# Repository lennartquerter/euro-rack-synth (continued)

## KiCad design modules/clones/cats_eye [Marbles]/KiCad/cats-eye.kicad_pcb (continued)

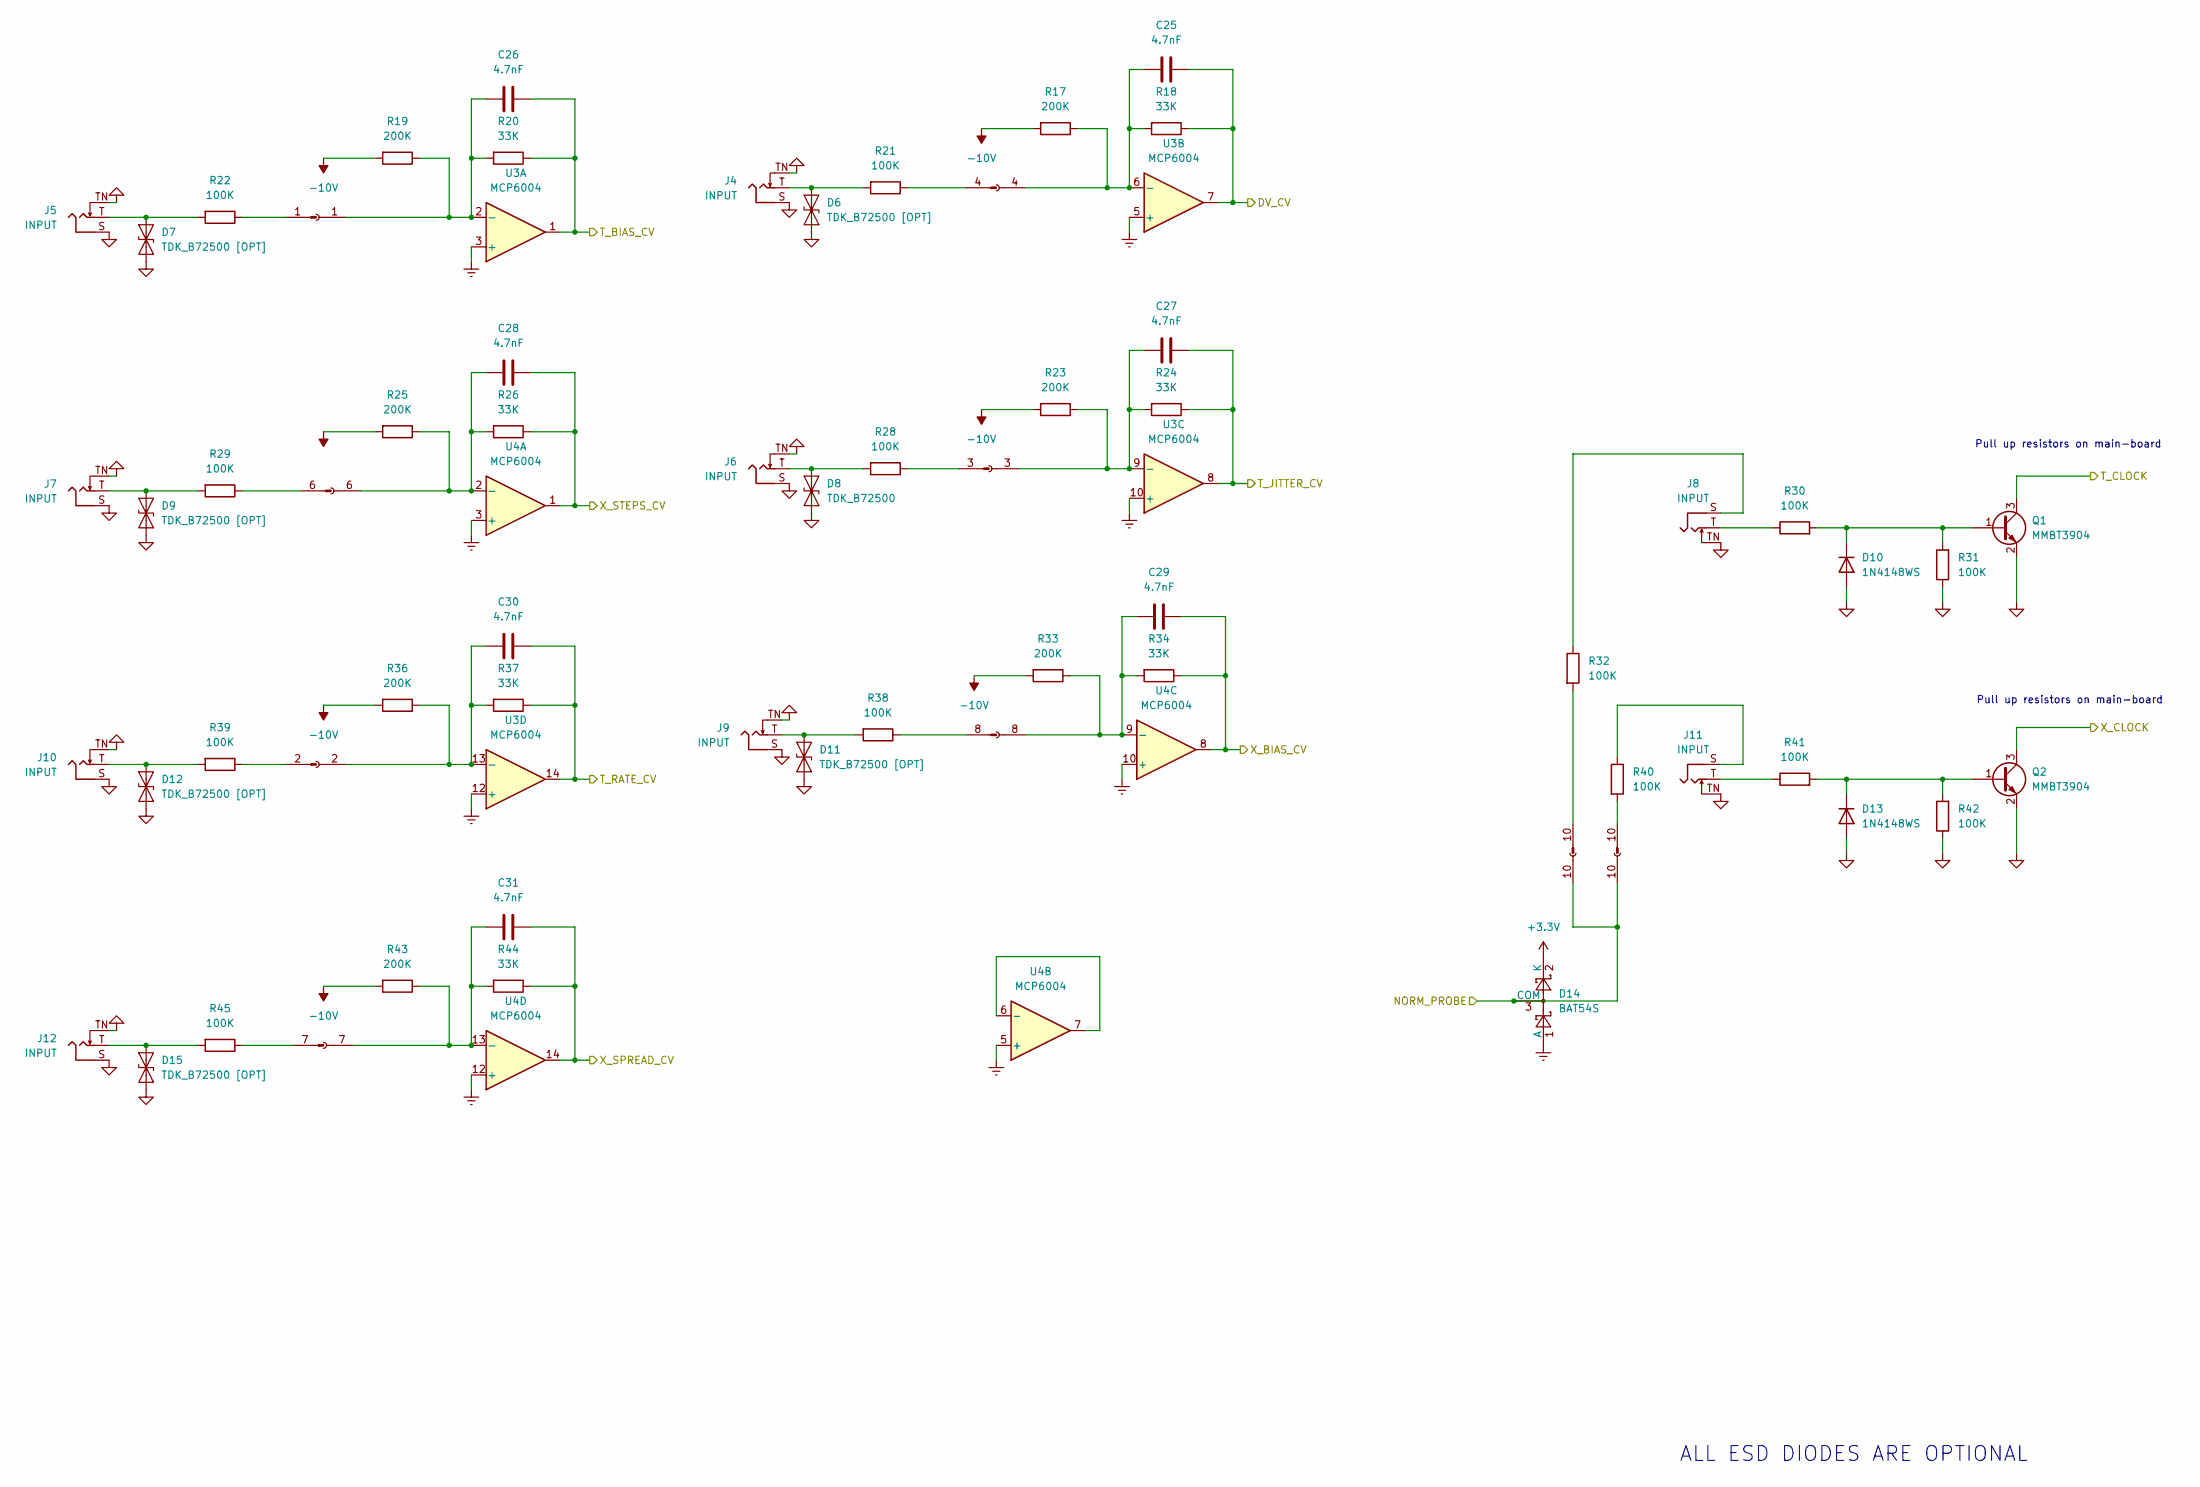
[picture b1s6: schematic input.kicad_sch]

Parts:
C25, C26, C27, C28, C29, C30, C31: 4.7nF; C_0805_2012Metric_Pad1.18x1.45mm_HandSolder
D6, D7, D9, D11, D12, D15: TDK_B72500 [OPT]; D_0603_1608Metric_Pad1.05x0.95mm_HandSolder
D8: TDK_B72500; D_0603_1608Metric_Pad1.05x0.95mm_HandSolder
D10, D13: 1N4148WS; D_SOD-323_HandSoldering
D14: BAT54S; SOT-23_Handsoldering
J4, J5, J6, J7, J8, J9, J10, J11, J12: INPUT; Jack_3.5mm_QingPu_WQP-PJ398SM_Vertical_CircularHoles
Q1, Q2: MMBT3904; SOT-23_Handsoldering
R17, R19, R23, R25, R33, R36, R43: 200K; R_0805_2012Metric_Pad1.20x1.40mm_HandSolder
R18, R20, R24, R26, R34, R37, R44: 33K; R_0805_2012Metric_Pad1.20x1.40mm_HandSolder
R21, R22, R28, R29, R30, R31, R32, R38, R39, R40, R41, R42, R45: 100K; R_0805_2012Metric_Pad1.20x1.40mm_HandSolder
U3, U4: MCP6004; SOIC-14
XP1, XP3: Conn_01x16_Socket; PinSocket_1x16_P2.54mm_Vertical
XP2, XP4: Conn_01x16_Pin; PinHeader_1x16_P2.54mm_Vertical
XP5: Conn_01x08_Socket; PinSocket_1x08_P2.54mm_Vertical
XP6: Conn_01x08_Pin; PinHeader_1x08_P2.54mm_Vertical

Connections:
+3.3V: D14.2 (K); also elsewhere on the board
-10V: R17.2, R19.2, R23.2, R25.2, R33.2, R36.2, R43.2; also elsewhere on the board
/input/DV_CV: C25.1, R18.1, U3.7; also elsewhere on the board
/input/NORM_PROBE: D14.3 (COM), XP1.10, XP3.10; also elsewhere on the board
/input/T_BIAS_CV: C26.1, R20.1, U3.1; also elsewhere on the board
/input/T_CLOCK: Q1.3 (C); also elsewhere on the board
/input/T_JITTER_CV: C27.1, R24.1, U3.8; also elsewhere on the board
/input/T_RATE_CV: C30.1, R37.1, U3.14; also elsewhere on the board
/input/X_BIAS_CV: C29.1, R34.1, U4.8; also elsewhere on the board
/input/X_CLOCK: Q2.3 (C); also elsewhere on the board
/input/X_SPREAD_CV: C31.1, R44.1, U4.14; also elsewhere on the board
/input/X_STEPS_CV: C28.1, R26.1, U4.1; also elsewhere on the board
GND: D6.2 (A2), D7.2 (A2), D8.2 (A2), D9.2 (A2), D10.2 (A), D11.2 (A2), D12.2 (A2), D13.2 (A), D15.2 (A2), J4.S, J4.TN, J5.S, J5.TN, J6.S, J6.TN, J7.S, J7.TN, J8.TN, J9.S, J9.TN, J10.S, J10.TN, J11.TN, J12.S, J12.TN, Q1.2 (E), Q2.2 (E), R31.1, R42.1; also elsewhere on the board
GNDREF: D14.1 (A), U3.3 (+), U3.5 (+), U3.10 (+), U3.12 (+), U4.3 (+), U4.5 (+), U4.10 (+), U4.12 (+); also elsewhere on the board
unnamed: D6.1 (A1), J4.T, R21.2
unnamed: D7.1 (A1), J5.T, R22.2
unnamed: D8.1 (A1), J6.T, R28.2
unnamed: D9.1 (A1), J7.T, R29.2
unnamed: D10.1 (K), Q1.1 (B), R30.2, R31.2
unnamed: D11.1 (A1), J9.T, R38.2
unnamed: D12.1 (A1), J10.T, R39.2
unnamed: D13.1 (K), Q2.1 (B), R41.2, R42.2
unnamed: D15.1 (A1), J12.T, R45.2
unnamed: J8.S, R32.1
unnamed: J8.T, R30.1
unnamed: J11.S, R40.1
unnamed: J11.T, R41.1
unnamed: C26.2, R19.1, R20.2, U3.2 (-), XP5.1
unnamed: C25.2, R17.1, R18.2, U3.6 (-), XP5.4
unnamed: C27.2, R23.1, R24.2, U3.9 (-), XP5.3
unnamed: C30.2, R36.1, R37.2, U3.13 (-), XP5.2
unnamed: C28.2, R25.1, R26.2, U4.2 (-), XP5.6
unnamed: U4.6 (-), U4.7
unnamed: C29.2, R33.1, R34.2, U4.9 (-), XP5.8
unnamed: C31.2, R43.1, R44.2, U4.13 (-), XP5.7
unnamed: R32.2, XP2.10
unnamed: R40.2, XP4.10
unnamed: R22.1, XP6.1
unnamed: R39.1, XP6.2
unnamed: R28.1, XP6.3
unnamed: R21.1, XP6.4
unnamed: R29.1, XP6.6
unnamed: R45.1, XP6.7
unnamed: R38.1, XP6.8

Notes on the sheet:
ALL ESD DIODES ARE OPTIONAL
Pull up resistors on main-board

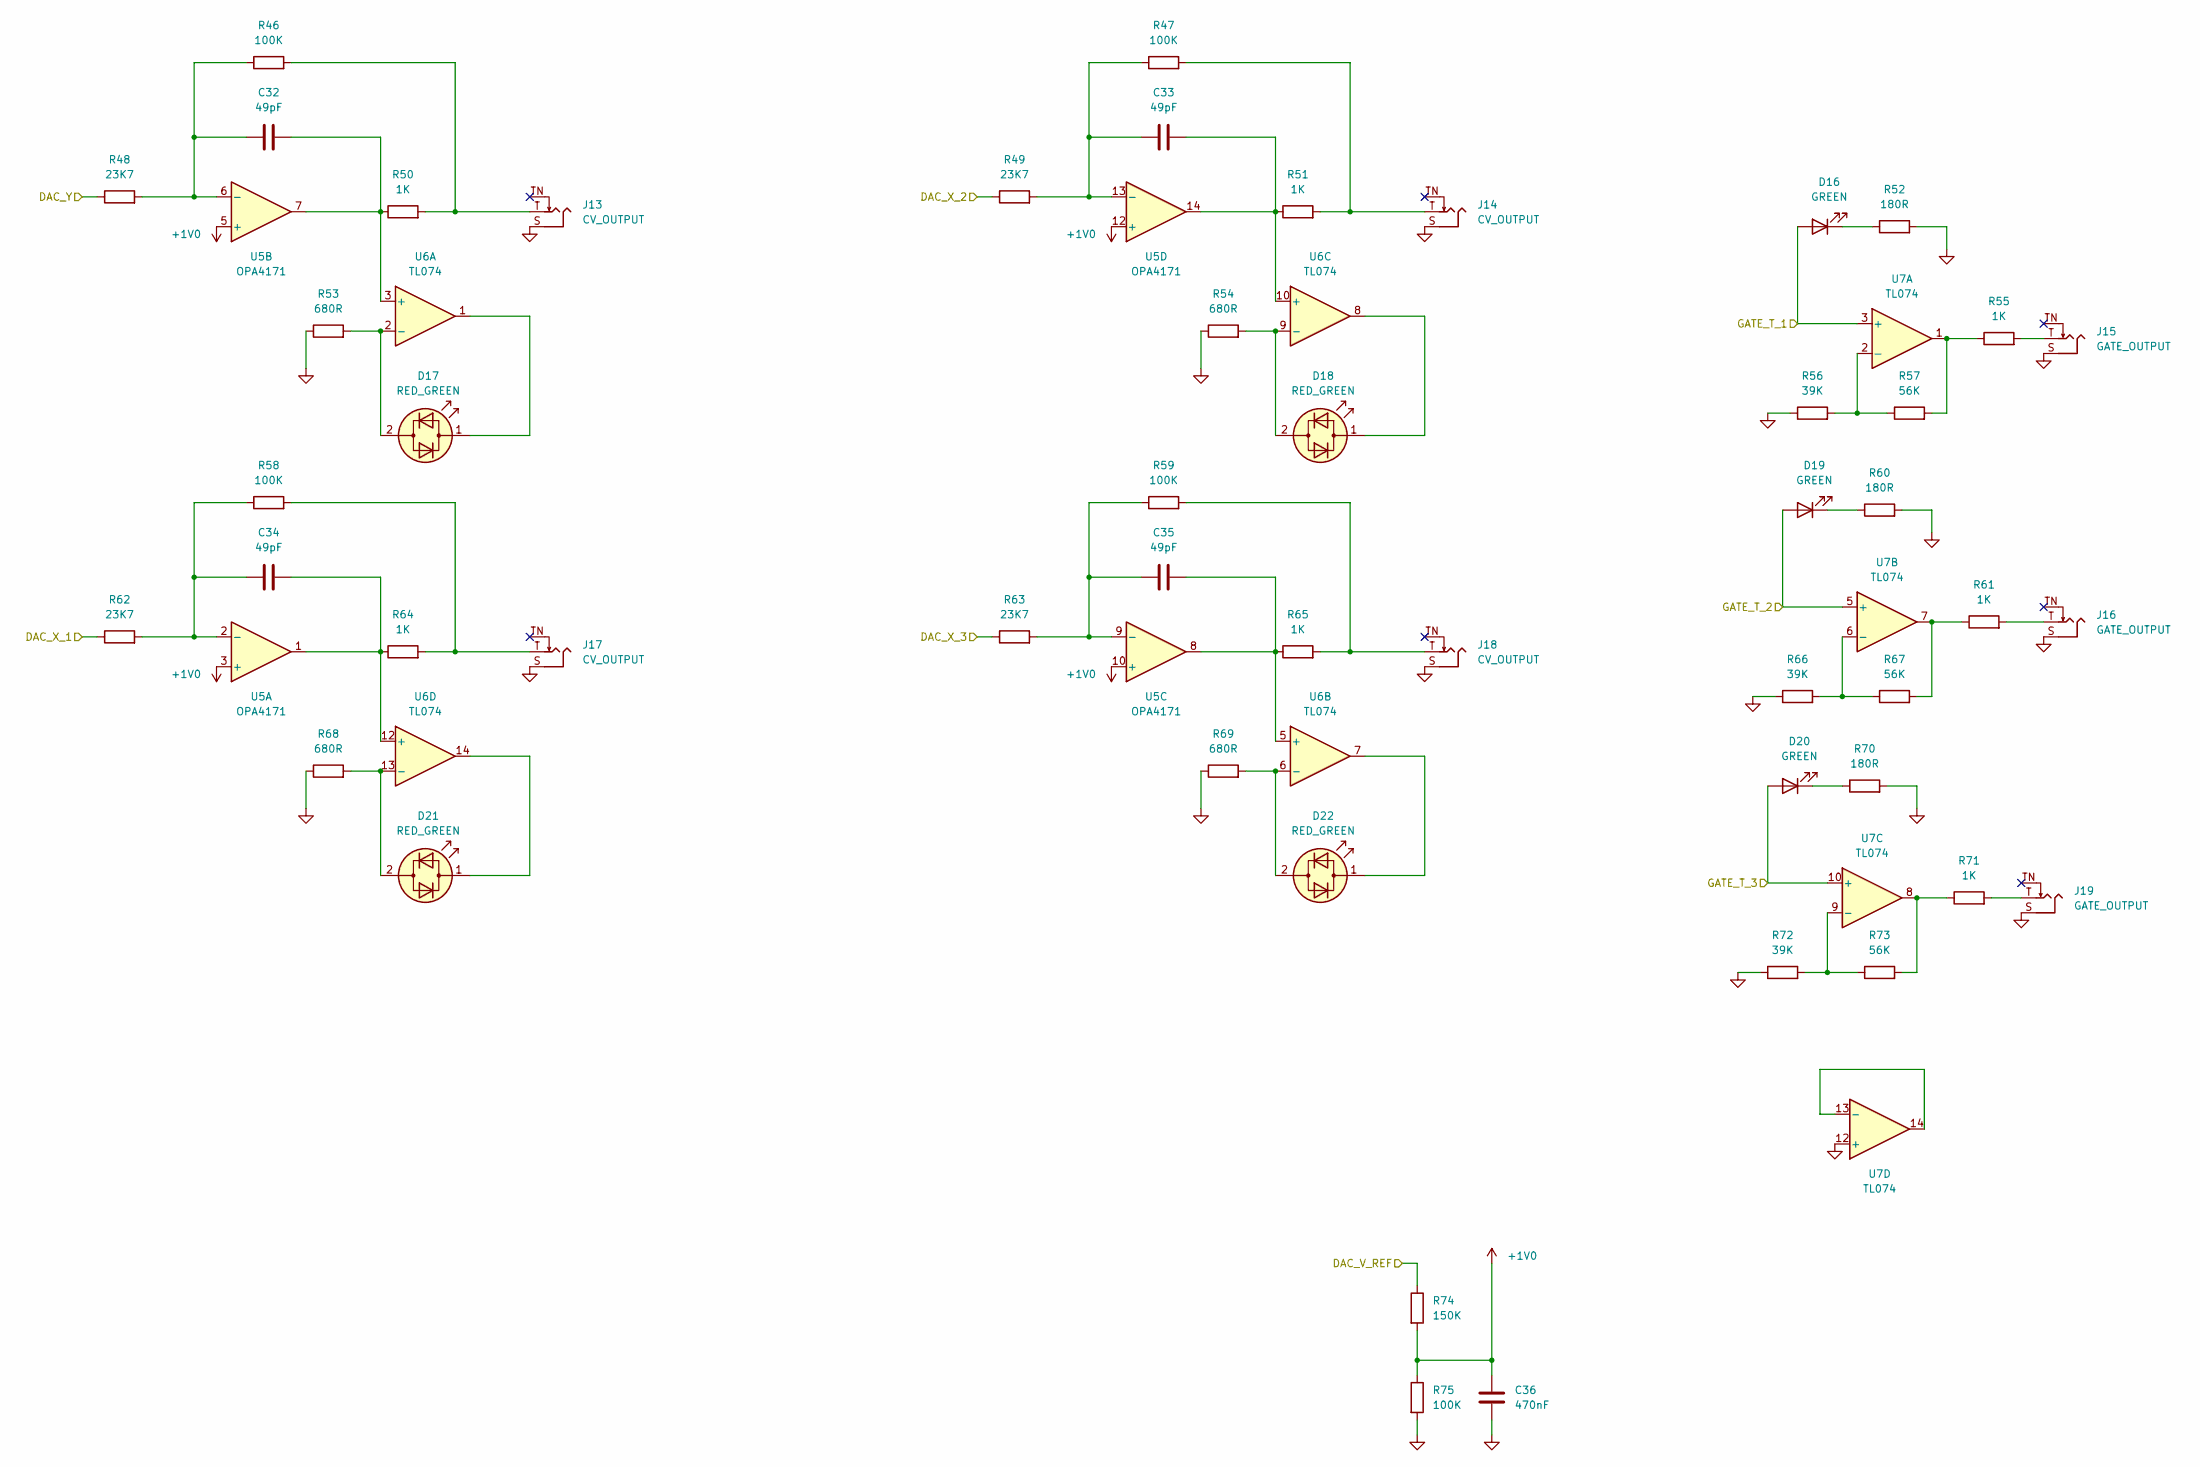
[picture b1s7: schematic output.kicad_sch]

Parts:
C32, C33, C34, C35: 49pF; C_0805_2012Metric_Pad1.18x1.45mm_HandSolder
C36: 470nF; C_0805_2012Metric_Pad1.18x1.45mm_HandSolder
D16, D19, D20: GREEN; LED_D3.0mm_SM
D17, D18, D21, D22: RED_GREEN; LED_D3.0mm_SM
J13, J14, J17, J18: CV_OUTPUT; Jack_3.5mm_QingPu_WQP-PJ398SM_SM
J15, J16, J19: GATE_OUTPUT; Jack_3.5mm_QingPu_WQP-PJ398SM_SM
R46, R47, R58, R59, R75: 100K; R_0805_2012Metric_Pad1.20x1.40mm_HandSolder
R48, R49, R62, R63: 23K7; R_0805_2012Metric_Pad1.20x1.40mm_HandSolder
R50, R51, R55, R61, R64, R65, R71: 1K; R_0805_2012Metric_Pad1.20x1.40mm_HandSolder
R52, R60, R70: 180R; R_0805_2012Metric_Pad1.20x1.40mm_HandSolder
R53, R54, R68, R69: 680R; R_0805_2012Metric_Pad1.20x1.40mm_HandSolder
R56, R66, R72: 39K; R_0805_2012Metric_Pad1.20x1.40mm_HandSolder
R57, R67, R73: 56K; R_0805_2012Metric_Pad1.20x1.40mm_HandSolder
R74: 150K; R_0805_2012Metric_Pad1.20x1.40mm_HandSolder
U5: OPA4171; SOIC-14
U6, U7: TL074; SOIC-14

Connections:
+1V0: C36.2, R74.2, R75.1, U5.3 (+), U5.5 (+), U5.10 (+), U5.12 (+)
/output/DAC_V_REF: R74.1; also elsewhere on the board
/output/DAC_X_1: R62.1; also elsewhere on the board
/output/DAC_X_2: R49.1; also elsewhere on the board
/output/DAC_X_3: R63.1; also elsewhere on the board
/output/DAC_Y: R48.1; also elsewhere on the board
/output/GATE_T_1: D16.2 (A), U7.3 (+); also elsewhere on the board
/output/GATE_T_2: D19.2 (A), U7.5 (+); also elsewhere on the board
/output/GATE_T_3: D20.2 (A), U7.10 (+); also elsewhere on the board
GND: C36.1, J13.S, J14.S, J15.S, J16.S, J17.S, J18.S, J19.S, R52.2, R53.1, R54.1, R56.1, R60.2, R66.1, R68.1, R69.1, R70.2, R72.1, R75.2, U7.12 (+); also elsewhere on the board
unnamed: D16.1 (K), R52.1
unnamed: D17.2 (AK), R53.2, U6.2 (-)
unnamed: D17.1 (KA), U6.1
unnamed: D18.2 (AK), R54.2, U6.9 (-)
unnamed: D18.1 (KA), U6.8
unnamed: D19.1 (K), R60.1
unnamed: D20.1 (K), R70.1
unnamed: D21.2 (AK), R68.2, U6.13 (-)
unnamed: D21.1 (KA), U6.14
unnamed: D22.2 (AK), R69.2, U6.6 (-)
unnamed: D22.1 (KA), U6.7
unnamed: J13.T, R46.2, R50.2
unnamed: J14.T, R47.2, R51.2
unnamed: J15.T, R55.2
unnamed: J16.T, R61.2
unnamed: J17.T, R58.2, R64.2
unnamed: J18.T, R59.2, R65.2
unnamed: J19.T, R71.2
unnamed: R55.1, R57.2, U7.1
unnamed: R61.1, R67.2, U7.7
unnamed: R71.1, R73.2, U7.8
unnamed: C34.2, R58.1, R62.2, U5.2 (-)
unnamed: C32.2, R46.1, R48.2, U5.6 (-)
unnamed: C35.2, R59.1, R63.2, U5.9 (-)
unnamed: C33.2, R47.1, R49.2, U5.13 (-)
unnamed: C32.1, R50.1, U5.7, U6.3 (+)
unnamed: C35.1, R65.1, U5.8, U6.5 (+)
unnamed: C33.1, R51.1, U5.14, U6.10 (+)
unnamed: C34.1, R64.1, U5.1, U6.12 (+)
unnamed: R56.2, R57.1, U7.2 (-)
unnamed: R66.2, R67.1, U7.6 (-)
unnamed: R72.2, R73.1, U7.9 (-)
unnamed: U7.13 (-), U7.14

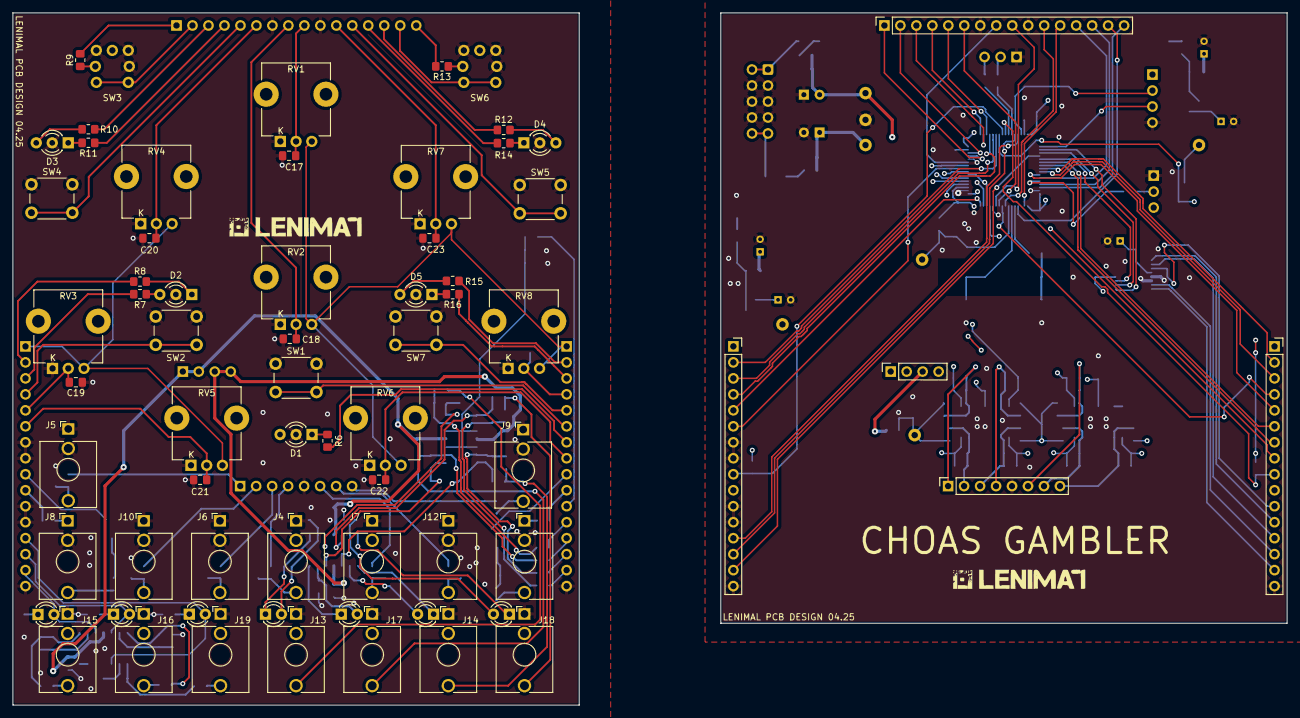
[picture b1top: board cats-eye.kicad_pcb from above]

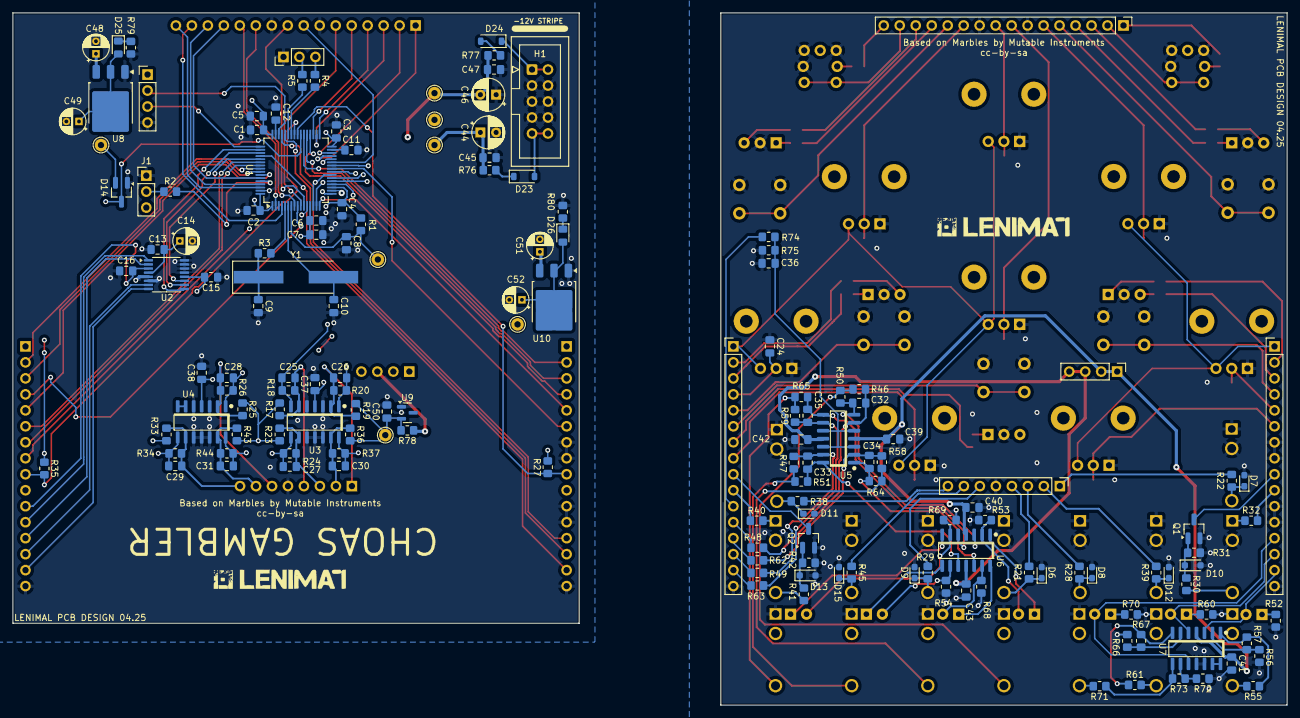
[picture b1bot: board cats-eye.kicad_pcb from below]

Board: 4 copper layers, 202.5 x 110.0 mm, 223 parts (157 on the bottom side), 188 nets.

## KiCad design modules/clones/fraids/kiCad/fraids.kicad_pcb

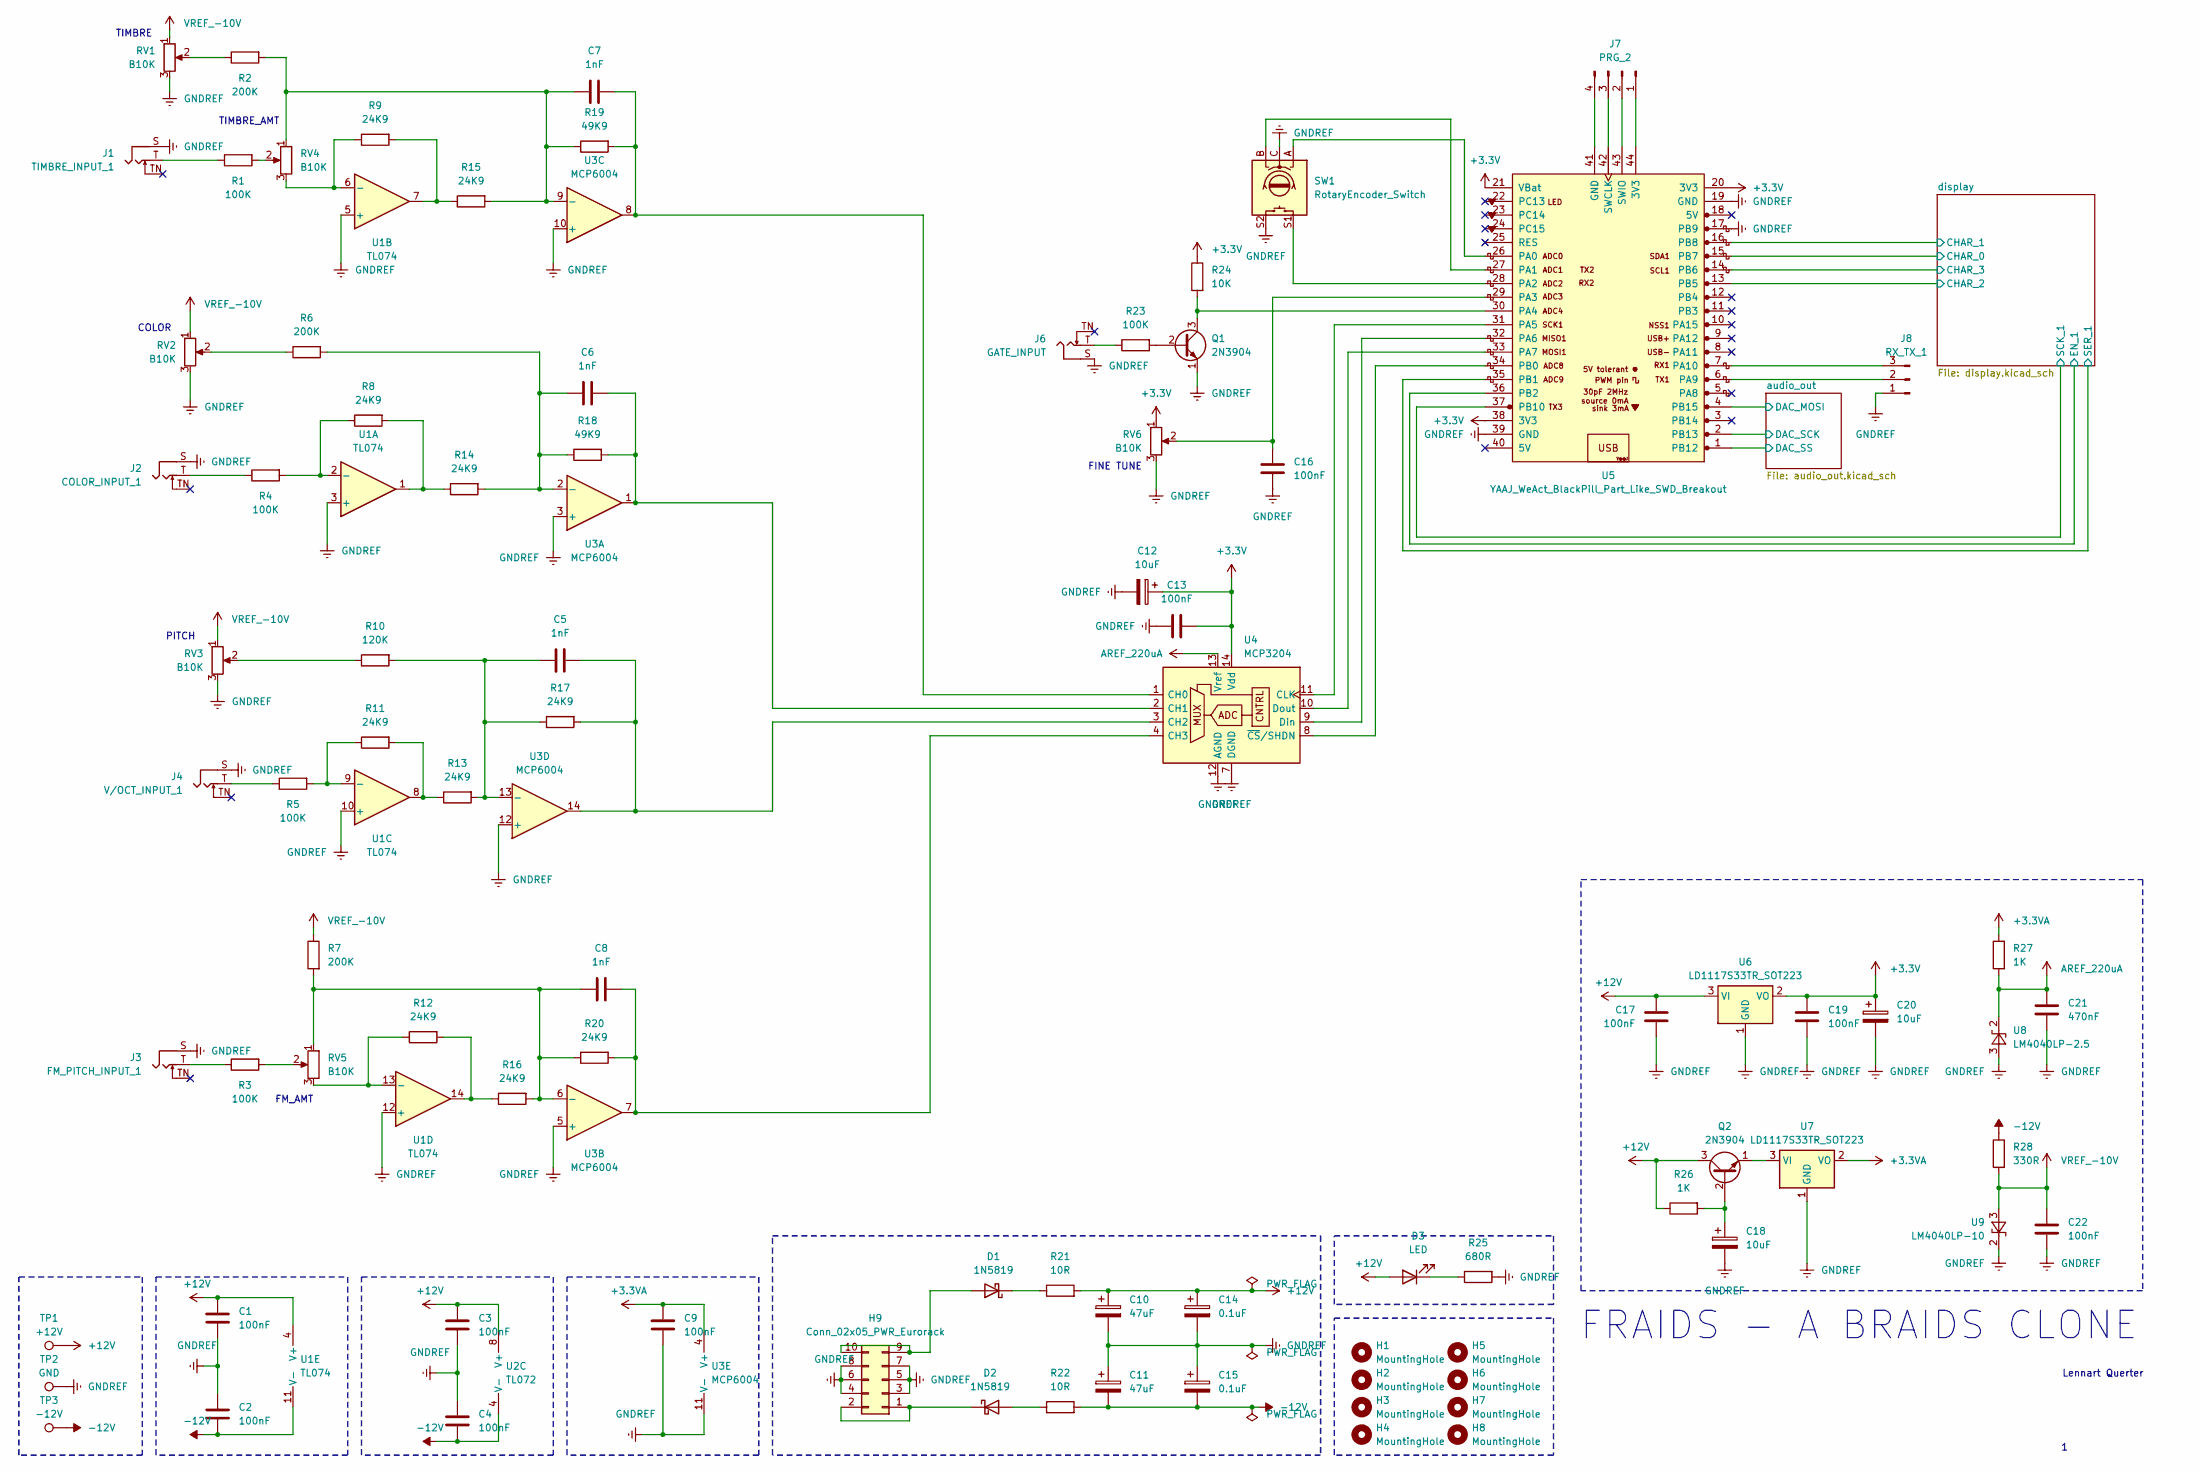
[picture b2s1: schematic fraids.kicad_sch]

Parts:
C1, C2, C3, C4, C9, C13, C16, C17, C19, C22: 100nF; C_Disc_D7.0mm_W2.5mm_P5.00mm
C5, C6, C7, C8: 1nF; C_Disc_D7.0mm_W2.5mm_P5.00mm
C10, C11: 47uF; CP_Radial_D6.3mm_P2.50mm
C12, C18, C20: 10uF; CP_Radial_D5.0mm_P2.50mm
C14, C15: 0.1uF; CP_Radial_D4.0mm_P2.00mm
C21: 470nF; C_Disc_D7.0mm_W2.5mm_P5.00mm
D1, D2: 1N5819; D_DO-41_SOD81_P10.16mm_Horizontal
D3: LED; LED_D5.0mm (center Aligned)
H1, H2, H3, H4, H5, H6, H7, H8: MountingHole; MountingHole_3.2mm_M3
H9: Conn_02x05_PWR_Eurorack; IDC-Header_2x05_P2.54mm_Vertical
J1: TIMBRE_INPUT_1; Jack_3.5mm_QingPu_WQP-PJ398SM_Vertical_CircularHoles
J2: COLOR_INPUT_1; Jack_3.5mm_QingPu_WQP-PJ398SM_Vertical_CircularHoles
J3: FM_PITCH_INPUT_1; Jack_3.5mm_QingPu_WQP-PJ398SM_Vertical_CircularHoles
J4: V/OCT_INPUT_1; Jack_3.5mm_QingPu_WQP-PJ398SM_Vertical_CircularHoles
J6: GATE_INPUT; Jack_3.5mm_QingPu_WQP-PJ398SM_Vertical_CircularHoles
J7: PRG_2; PinHeader_1x04_P2.54mm_Vertical
J8: RX_TX_1; PinHeader_1x03_P2.54mm_Vertical
Q1, Q2: 2N3904; TO-92_Inline
R1, R3, R4, R5, R23: 100K; R_Default (DIN0207)
R2, R6, R7: 200K; R_Default (DIN0207)
R8, R9, R11, R12, R13, R14, R15, R16, R17, R20: 24K9; R_Default (DIN0207)
R10: 120K; R_Default (DIN0207)
R18, R19: 49K9; R_Default (DIN0207)
R21, R22: 10R; R_Default (DIN0207)
R24: 10K; R_Default (DIN0207)
R25: 680R; R_Default (DIN0207)
R26, R27: 1K; R_Default (DIN0207)
R28: 330R; R_Default (DIN0207)
RV1, RV2, RV3, RV4, RV5, RV6: B10K; Potentiometer_TT_P0915N
SW1: RotaryEncoder_Switch; RotaryEncoder_Alps_EC11E-Switch_Vertical_H20mm
TP1: +12V; Pin_D1.0mm_L10.0mm
TP2: GND; Pin_D1.0mm_L10.0mm
TP3: -12V; Pin_D1.0mm_L10.0mm
U1: TL074; DIP-14_W7.62mm_Socket_LongPads
U2: TL072; DIP-14_W7.62mm_Socket_LongPads
U3: MCP6004; DIP-14_W7.62mm_Socket_LongPads
U4: MCP3204; DIP-14_W7.62mm_Socket_LongPads
U5: YAAJ_WeAct_BlackPill_Part_Like_SWD_Breakout; YAAJ_WeAct_BlackPill_SWD_2
U6, U7: LD1117S33TR_SOT223; TO-218-3_Horizontal_TabDown
U8: LM4040LP-2.5; TO-92_Inline
U9: LM4040LP-10; TO-92_Inline

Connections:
+3.3V: C12.1, C13.2, C19.1, C20.1, R24.2, RV6.1, U4.14 (Vdd), U5.20 (3V3), U5.21 (VBat), U5.38 (3V3), U6.2 (VO); also elsewhere on the board
+3.3VA: C9.1, R27.2, U3.4 (V+), U7.2 (VO)
+12V: C1.1, C3.1, C10.1, C14.1, C17.1, D3.2 (A), Q2.3 (C), R21.2, R26.2, TP1.1, U1.4 (V+), U2.8 (V+), U6.3 (VI)
-12V: C2.2, C4.2, C11.2, C15.2, R22.2, R28.2, TP3.1, U1.11 (V-), U2.4 (V-)
/audio_out/DAC_MOSI: U5.4 (PB15); also elsewhere on the board
/audio_out/DAC_SCK: U5.2 (PB13); also elsewhere on the board
/audio_out/DAC_SS: U5.1 (PB12); also elsewhere on the board
/display/CHAR_0: U5.15 (PB7); also elsewhere on the board
/display/CHAR_1: U5.16 (PB8); also elsewhere on the board
/display/CHAR_2: U5.13 (PB5); also elsewhere on the board
/display/CHAR_3: U5.14 (PB6); also elsewhere on the board
/display/EN_1: U5.36 (PB2); also elsewhere on the board
/display/SCK_1: U5.37 (PB10); also elsewhere on the board
/display/SER_1: U5.35 (PB1); also elsewhere on the board
AREF_220uA: C21.1, R27.1, U4.13 (Vref), U8.2 (K)
GNDREF: C1.2, C2.1, C3.2, C4.1, C9.2, C10.2, C11.1, C12.2, C13.1, C14.2, C15.1, C16.2, C17.2, C18.2, C19.2, C20.2, C21.2, C22.2, H9.3, H9.4, H9.5, H9.6, H9.7, H9.8, J1.S, J2.S, J3.S, J4.S, J6.S, J8.1, Q1.1 (E), R25.1, RV1.3, RV2.3, RV3.3, RV6.3, SW1.C, SW1.S2, TP2.1, U1.3 (+), U1.5 (+), U1.10 (+), U1.12 (+), U3.3 (+), U3.5 (+), U3.10 (+), U3.11 (V-), U3.12 (+), U4.7 (DGND), U4.12 (AGND), U5.17 (PB9), U5.19 (GND), U5.39 (GND), U6.1 (GND), U7.1 (GND), U8.3 (A), U9.2 (K); also elsewhere on the board
unnamed: D1.2 (A), H9.9, H9.10
unnamed: D1.1 (K), R21.1
unnamed: D2.2 (A), R22.1
unnamed: D2.1 (K), H9.1, H9.2
unnamed: D3.1 (K), R25.2
unnamed: J1.T, R1.2
unnamed: J2.T, R4.2
unnamed: J3.T, R3.2
unnamed: J4.T, R5.2
unnamed: J6.T, R23.2
unnamed: J7.1, U5.44 (3V3)
unnamed: J7.2, U5.43 (SWIO)
unnamed: J7.3, U5.42 (SWCLK)
unnamed: J7.4, U5.41 (GND)
unnamed: J8.2, U5.6 (PA9)
unnamed: J8.3, U5.7 (PA10)
unnamed: Q1.2 (B), R23.1
unnamed: Q1.3 (C), R24.1, U5.30 (PA4)
unnamed: C18.1, Q2.2 (B), R26.1
unnamed: Q2.1 (E), U7.3 (VI)
unnamed: R1.1, RV4.2
unnamed: R2.2, RV1.2
unnamed: R3.1, RV5.2
unnamed: R6.2, RV2.2
unnamed: R10.2, RV3.2
unnamed: R11.1, R13.2, U1.8
unnamed: R12.1, R16.2, U1.14
unnamed: R8.1, R14.2, U1.1
unnamed: R9.1, R15.2, U1.7
unnamed: R4.1, R8.2, U1.2 (-)
unnamed: R9.2, RV4.3, U1.6 (-)
unnamed: R5.1, R11.2, U1.9 (-)
unnamed: R12.2, RV5.3, U1.13 (-)
unnamed: C6.1, R6.1, R14.1, R18.2, U3.2 (-)
unnamed: C8.1, R7.1, R16.1, R20.2, RV5.1, U3.6 (-)
unnamed: C7.1, R2.1, R15.1, R19.2, RV4.1, U3.9 (-)
unnamed: C5.1, R10.1, R13.1, R17.2, U3.13 (-)
unnamed: C7.2, R19.1, U3.8, U4.1 (CH0)
unnamed: C6.2, R18.1, U3.1, U4.2 (CH1)
unnamed: C5.2, R17.1, U3.14, U4.3 (CH2)
unnamed: C8.2, R20.1, U3.7, U4.4 (CH3)
unnamed: U4.11 (CLK), U5.31 (PA5)
unnamed: U4.9 (Din), U5.32 (PA6)
unnamed: U4.10 (Dout), U5.33 (PA7)
unnamed: U4.8 (~CS/SHDN), U5.34 (PB0)
unnamed: SW1.A, U5.26 (PA0)
unnamed: SW1.B, U5.27 (PA1)
unnamed: SW1.S1, U5.28 (PA2)
unnamed: C16.1, RV6.2, U5.29 (PA3)
VREF_-10V: C22.1, R7.2, R28.1, RV1.1, RV2.1, RV3.1, U9.3 (A)

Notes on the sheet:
FINE TUNE
PITCH
TIMBRE
FM_AMT
COLOR
FRAIDS - A BRAIDS CLONE
TIMBRE_AMT
Lennart Querter

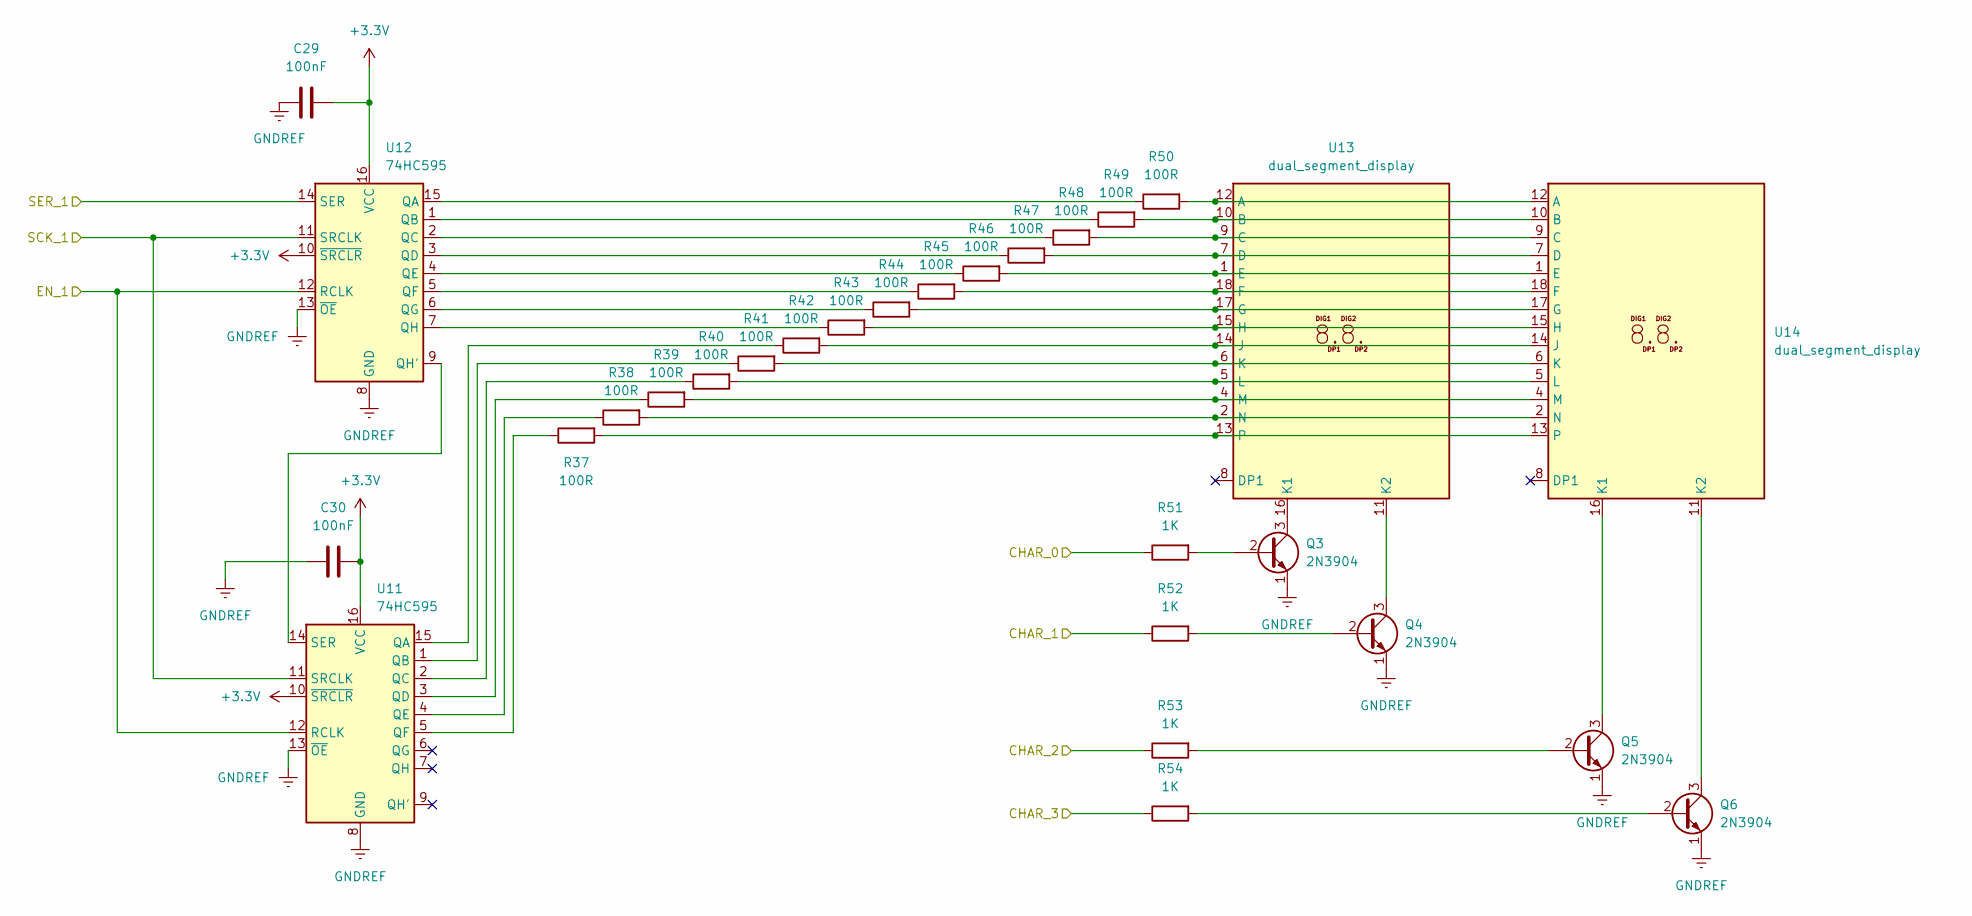
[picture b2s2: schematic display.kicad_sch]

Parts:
C29, C30: 100nF; C_Disc_D7.0mm_W2.5mm_P5.00mm
Q3, Q4, Q5, Q6: 2N3904; TO-92_Inline
R37, R38, R39, R40, R41, R42, R43, R44, R45, R46, R47, R48, R49, R50: 100R; R_Default (DIN0207)
R51, R52, R53, R54: 1K; R_Default (DIN0207)
U11, U12: 74HC595; DIP-16_W7.62mm_Socket_LongPads
U13, U14: dual_segment_display; DA56-11CGKWA

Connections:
+3.3V: C29.2, C30.2, U11.10 (~SRCLR), U11.16 (VCC), U12.10 (~SRCLR), U12.16 (VCC); also elsewhere on the board
/display/CHAR_0: R51.2; also elsewhere on the board
/display/CHAR_1: R52.2; also elsewhere on the board
/display/CHAR_2: R53.2; also elsewhere on the board
/display/CHAR_3: R54.2; also elsewhere on the board
/display/EN_1: U11.12 (RCLK), U12.12 (RCLK); also elsewhere on the board
/display/SCK_1: U11.11 (SRCLK), U12.11 (SRCLK); also elsewhere on the board
/display/SER_1: U12.14 (SER); also elsewhere on the board
GNDREF: C29.1, C30.1, Q3.1 (E), Q4.1 (E), Q5.1 (E), Q6.1 (E), U11.8 (GND), U11.13 (~OE), U12.8 (GND), U12.13 (~OE); also elsewhere on the board
unnamed: Q3.2 (B), R51.1
unnamed: Q3.3 (C), U13.16 (K1)
unnamed: Q4.2 (B), R52.1
unnamed: Q4.3 (C), U13.11 (K2)
unnamed: Q5.2 (B), R53.1
unnamed: Q5.3 (C), U14.16 (K1)
unnamed: Q6.2 (B), R54.1
unnamed: Q6.3 (C), U14.11 (K2)
unnamed: R42.2, U11.15 (QA)
unnamed: R41.2, U11.1 (QB)
unnamed: R40.2, U11.2 (QC)
unnamed: R39.2, U11.3 (QD)
unnamed: R38.2, U11.4 (QE)
unnamed: R37.2, U11.5 (QF)
unnamed: U11.14 (SER), U12.9 (QH')
unnamed: R50.2, U12.15 (QA)
unnamed: R49.2, U12.1 (QB)
unnamed: R48.2, U12.2 (QC)
unnamed: R47.2, U12.3 (QD)
unnamed: R46.2, U12.4 (QE)
unnamed: R45.2, U12.5 (QF)
unnamed: R44.2, U12.6 (QG)
unnamed: R43.2, U12.7 (QH)
unnamed: R50.1, U13.12 (A), U14.12 (A)
unnamed: R49.1, U13.10 (B), U14.10 (B)
unnamed: R48.1, U13.9 (C), U14.9 (C)
unnamed: R47.1, U13.7 (D), U14.7 (D)
unnamed: R46.1, U13.1 (E), U14.1 (E)
unnamed: R45.1, U13.18 (F), U14.18 (F)
unnamed: R44.1, U13.17 (G), U14.17 (G)
unnamed: R43.1, U13.15 (H), U14.15 (H)
unnamed: R42.1, U13.14 (J), U14.14 (J)
unnamed: R41.1, U13.6 (K), U14.6 (K)
unnamed: R40.1, U13.5 (L), U14.5 (L)
unnamed: R39.1, U13.4 (M), U14.4 (M)
unnamed: R38.1, U13.2 (N), U14.2 (N)
unnamed: R37.1, U13.13, U14.13

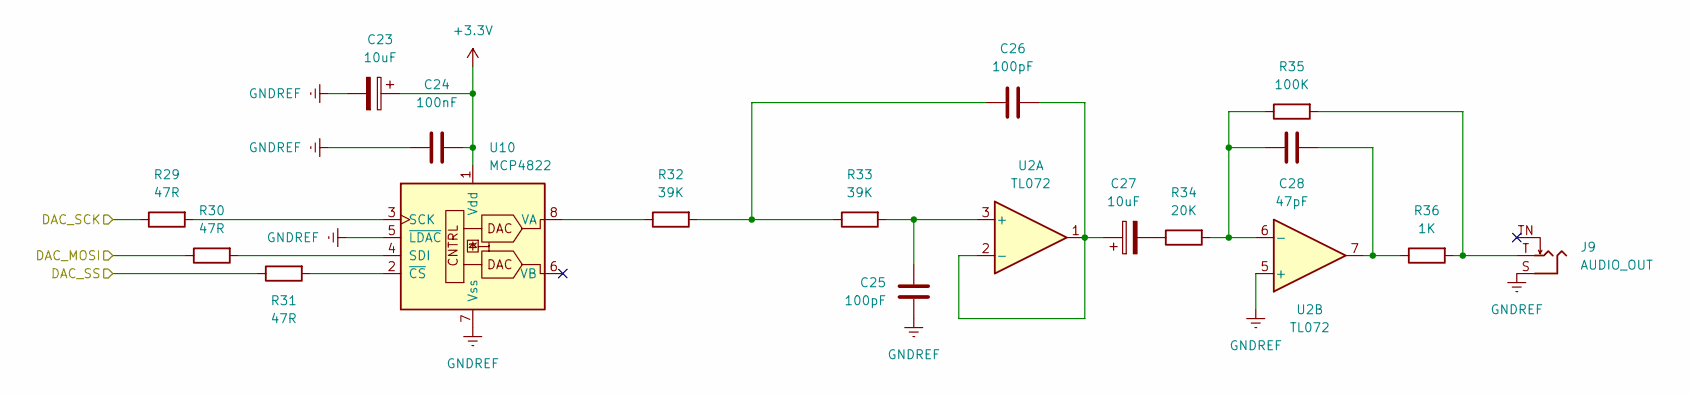
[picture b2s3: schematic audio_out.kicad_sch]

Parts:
C23, C27: 10uF; CP_Radial_D5.0mm_P2.50mm
C24: 100nF; C_Disc_D7.0mm_W2.5mm_P5.00mm
C25, C26: 100pF; C_Disc_D7.0mm_W2.5mm_P5.00mm
C28: 47pF; C_Disc_D7.0mm_W2.5mm_P5.00mm
J9: AUDIO_OUT; Jack_3.5mm_QingPu_WQP-PJ398SM_Vertical_CircularHoles
R29, R30, R31: 47R; R_Default (DIN0207)
R32, R33: 39K; R_Default (DIN0207)
R34: 20K; R_Default (DIN0207)
R35: 100K; R_Default (DIN0207)
R36: 1K; R_Default (DIN0207)
U2: TL072; DIP-14_W7.62mm_Socket_LongPads
U10: MCP4822; DIP-8_W7.62mm_Socket_LongPads

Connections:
+3.3V: C23.1, C24.2, U10.1 (Vdd); also elsewhere on the board
/audio_out/DAC_MOSI: R30.2; also elsewhere on the board
/audio_out/DAC_SCK: R29.2; also elsewhere on the board
/audio_out/DAC_SS: R31.2; also elsewhere on the board
GNDREF: C23.2, C24.1, C25.2, J9.S, U2.5 (+), U10.5 (~LDAC), U10.7 (Vss); also elsewhere on the board
unnamed: C26.1, R32.1, R33.2
unnamed: C27.2, R34.2
unnamed: C28.2, R36.2, U2.7
unnamed: J9.T, R35.1, R36.1
unnamed: C25.1, R33.1, U2.3 (+)
unnamed: C26.2, C27.1, U2.1, U2.2 (-)
unnamed: C28.1, R34.1, R35.2, U2.6 (-)
unnamed: R29.1, U10.3 (SCK)
unnamed: R30.1, U10.4 (SDI)
unnamed: R32.2, U10.8 (VA)
unnamed: R31.1, U10.2 (~CS)

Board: 2 copper layers, 134 parts (2 on the bottom side), 114 nets, no tracks yet.
